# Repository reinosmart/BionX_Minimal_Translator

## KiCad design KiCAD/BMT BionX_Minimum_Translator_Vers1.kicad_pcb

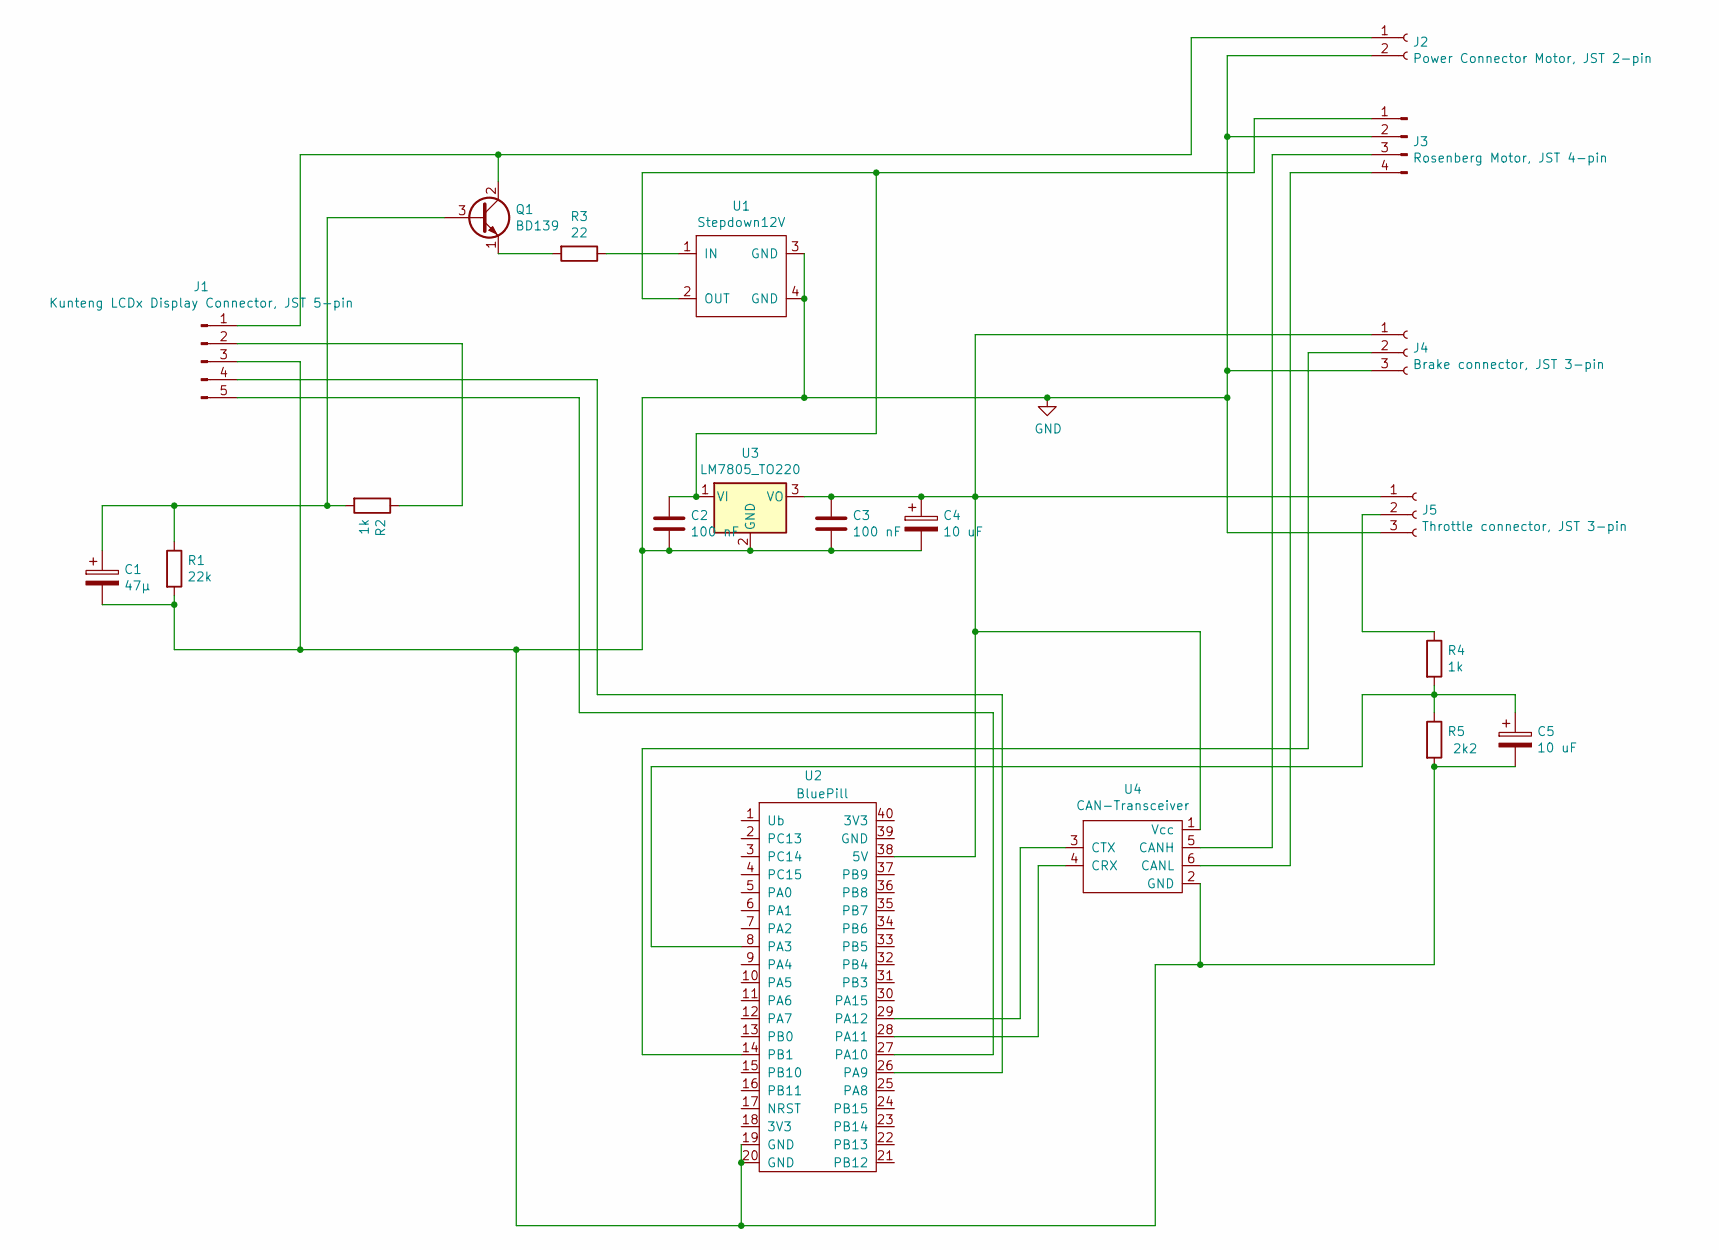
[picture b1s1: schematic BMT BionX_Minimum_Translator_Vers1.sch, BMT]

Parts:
C1: 47µ; CP_Radial_D7.5mm_P2.50mm
C2, C3: 100 nF; C_Rect_L7.2mm_W3.5mm_P5.00mm_FKS2_FKP2_MKS2_MKP2
C4, C5: 10 uF; CP_Radial_D5.0mm_P2.50mm
J1: Kunteng LCDx Display Connector, JST 5-pin; JST_EH_B5B-EH-A_1x05_P2.50mm_Vertical
J2: Power Connector Motor, JST 2-pin; JST_EH_B2B-EH-A_1x02_P2.50mm_Vertical
J3: Rosenberg Motor, JST 4-pin; JST_EH_B4B-EH-A_1x04_P2.50mm_Vertical
J4: Brake connector, JST 3-pin; JST_EH_B3B-EH-A_1x03_P2.50mm_Vertical
J5: Throttle connector, JST 3-pin; JST_EH_B3B-EH-A_1x03_P2.50mm_Vertical
Q1: BD139; TO-126-3_Horizontal_TabDown
R1: 22k; R_Axial_DIN0207_L6.3mm_D2.5mm_P7.62mm_Horizontal
R2, R4: 1k; R_Axial_DIN0207_L6.3mm_D2.5mm_P7.62mm_Horizontal
R3: 22; R_Axial_DIN0414_L11.9mm_D4.5mm_P15.24mm_Horizontal
R5: 2k2; R_Axial_DIN0207_L6.3mm_D2.5mm_P7.62mm_Horizontal
U1: Stepdown12V; Step-Down
U2: BluePill; DIP-40_BP
U3: LM7805_TO220; TO-220-3_Horizontal_TabDown
U4: CAN-Transceiver

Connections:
GND: C1.2, C2.2, C3.2, C4.2, C5.2, J1.3, J2.2, J3.2, J4.3, J5.3, R1.2, R5.2, U1.3 (GND), U1.4 (GND), U2.19 (GND), U2.20 (GND), U3.2 (GND), U4.2 (GND)
unnamed: C1.1, Q1.3 (B), R1.1, R2.2
unnamed: C2.1, J3.1, U1.2 (OUT), U3.1 (VI)
unnamed: C3.1, C4.1, J4.1, J5.1, U2.38 (5V), U3.3 (VO), U4.1 (Vcc)
unnamed: C5.1, R4.2, R5.1, U2.8 (PA3)
unnamed: J1.1, J2.1, Q1.2 (C)
unnamed: J1.2, R2.1
unnamed: J1.4, U2.26 (PA9)
unnamed: J1.5, U2.27 (PA10)
unnamed: J3.3, U4.5 (CANH)
unnamed: J3.4, U4.6 (CANL)
unnamed: J4.2, U2.14 (PB1)
unnamed: J5.2, R4.1
unnamed: Q1.1 (E), R3.2
unnamed: R3.1, U1.1 (IN)
unnamed: U2.28 (PA11), U4.4 (CRX)
unnamed: U2.29 (PA12), U4.3 (CTX)

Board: 2 copper layers, 20 parts (0 on the bottom side), 17 nets, no tracks yet.
